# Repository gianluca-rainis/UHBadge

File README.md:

# UHBadge

Universal Hacker Badge - The ultimate badge for hackers.

## Author
The author of the whole project is: 
**Gianluca Rainis** - [gianluca-rainis](https://github.com/gianluca-rainis) on GitHub.

## License
### Hardware design files (schematics, PCB, BOM):
Licensed under [CERN-OHL-S v2.0](LICENSE-CERN-OHL-S.md)

### Software, firmware and documentation:
Licensed under the [MIT License](LICENSE-MIT.md)

## AI Disclaimer
**No AI was used in the conception, design, or engineering of the hardware.**
Every circuit and every design decision are the original work of the author.

*AI tools* were used as **writing assistants** for parts of the firmware, to help write technical drivers and low-level functions.
**All content has been reviewed, verified, and edited by the author.**

## Development Tools
- **PCB Design:** KiCad
- **Documentation and code:** Visual Studio Code

## PCB Manufacturing
The Gerber files for PCB manufacturing are available in the [`gerber/`](gerber/) directory.

## Project Structure
```
UHBadge/
├── CustomFootprints.pretty/  # Custom footprints
├── firmware/                 # The RP2350 firmware
├── gerber/                   # PCB manufacturing files (Gerber format)
├── images/                   # Documentation images
├── .gitattributes            # Gitattributes file
├── .gitignore                # Gitignore file
├── gerber.zip                # Zip folder with all the gerber files
├── UHBadge.kicad_pcb         # PCB layout file
├── UHBadge.kicad_pro         # KiCad project file
├── UHBadge.kicad_sch         # Schematic file
├── UHBadge.step              # 3D model
├── BOM.csv                   # Bill Of Materials
├── LICENSE-CERN-OHL-S.md     # CERN-OHL-S License
├── LICENSE-MIT.md            # MIT License
└── README.md                 # This file
```

## Technical Details
- **Size**: 70mm x 117.6mm
- **Layers**: 2
- **Supply Voltage**: 3v3

## Build the firmware
From the directory of the repo:
```bash
cd firmware/build

cmake ..
make -j$(sysctl -n hw.ncpu)
```

You'll find the `UHBadge.uf2` file in the `firmware/build` directory.

## Hardware
### Schematic

### PCB

### 3D Render

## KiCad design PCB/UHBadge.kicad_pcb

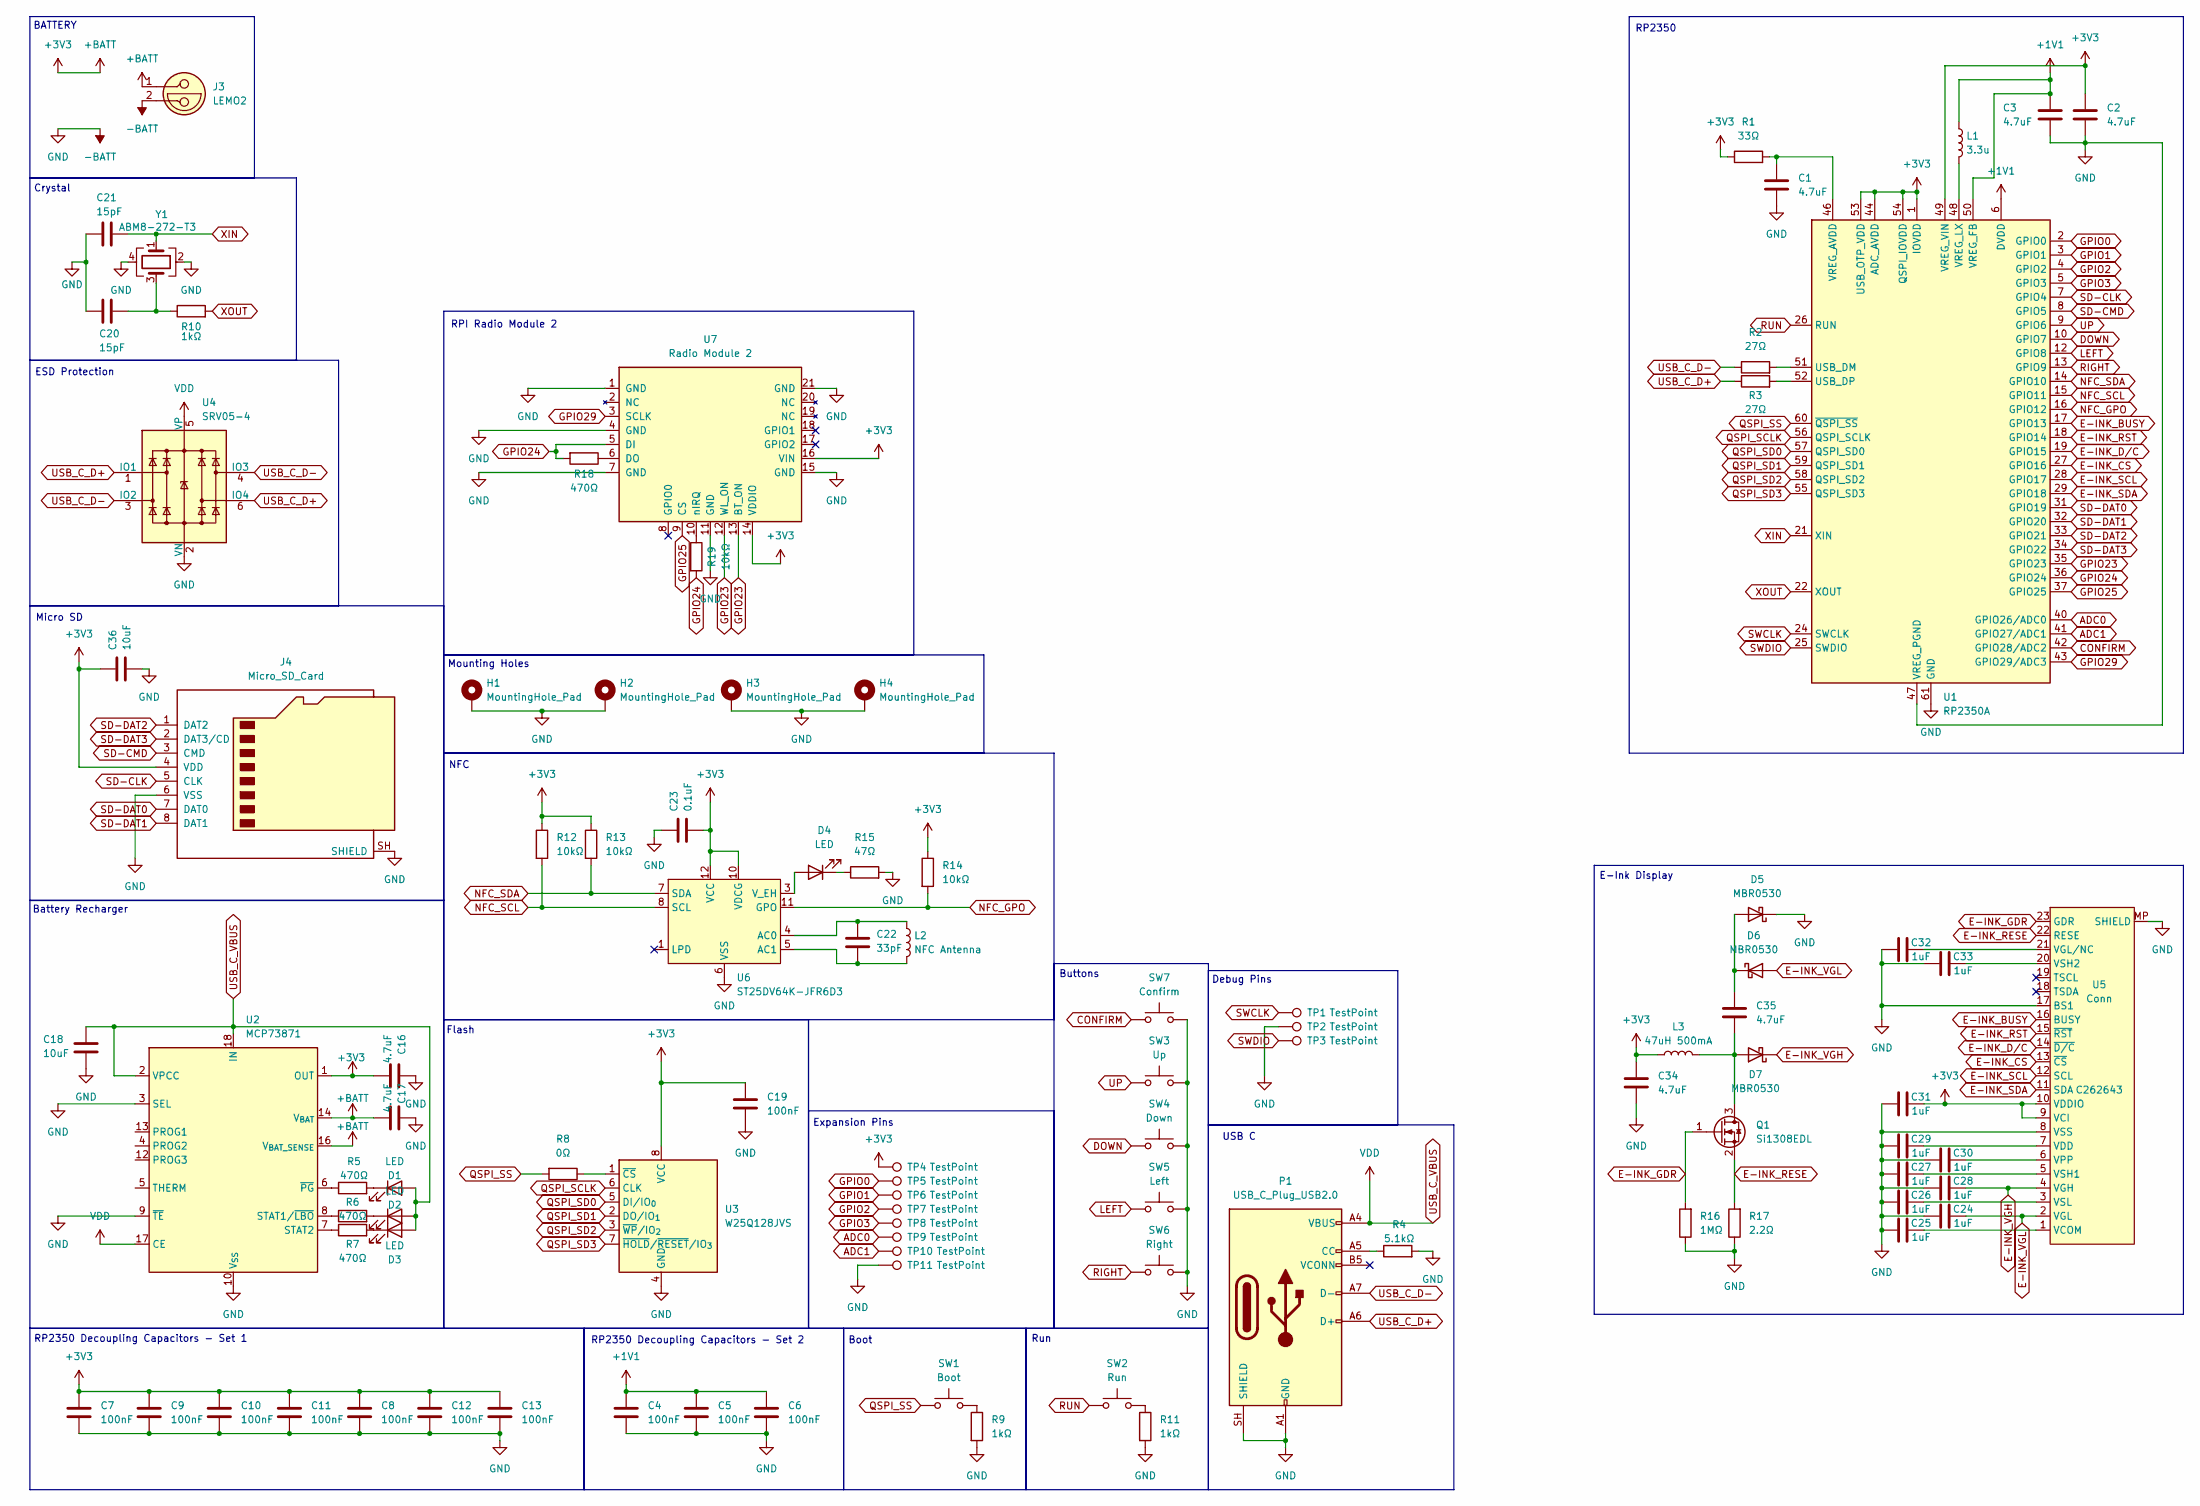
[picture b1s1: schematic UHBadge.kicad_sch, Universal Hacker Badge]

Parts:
C1, C2, C3, C16, C17, C34, C35: 4.7uF; C_0402_1005Metric
C4, C5, C6, C7, C8, C9, C10, C11, C12, C13, C19: 100nF; C_0402_1005Metric
C18, C36: 10uF; C_0402_1005Metric
C20, C21: 15pF; C_0402_1005Metric
C22: 33pF; C_0402_1005Metric
C23: 0.1uF; C_0402_1005Metric
C24, C25, C26, C27, C28, C29, C30, C31, C32, C33: 1uF; C_0402_1005Metric
D1, D2, D3, D4: LED; LED_0805_2012Metric
D5, D6, D7: MBR0530; D_SOD-123
H1, H2, H3, H4: MountingHole_Pad; MountingHole_2.2mm_M2_Pad_Via
J3: LEMO2; Molex_CLIK-Mate_502494-0270_1x02-1MP_P2.00mm_Horizontal
J4: Micro_SD_Card; microSD_HC_Hirose_DM3AT-SF-PEJM5
L1: 3.3u; Inductor
L2: NFC Antenna; NFC_Antenna
L3: 47uH 500mA; L_APV_ANR4018
P1: USB_C_Plug_USB2.0; USB_C_Receptacle_GCT_USB4105-xx-A_16P_TopMnt_Horizontal
Q1: Si1308EDL; SOT-323_SC-70
R1: 33Ω; R_0402_1005Metric
R2, R3: 27Ω; R_0402_1005Metric
R4: 5.1kΩ; R_0402_1005Metric
R5, R6, R7, R18: 470Ω; R_0402_1005Metric
R8: 0Ω; R_0402_1005Metric
R9, R10, R11: 1kΩ; R_0402_1005Metric
R12, R13, R14, R19: 10kΩ; R_0402_1005Metric
R15: 47Ω; R_0402_1005Metric
R16: 1MΩ; R_0402_1005Metric
R17: 2.2Ω; R_0402_1005Metric
SW1: Boot; SW_SPST_EVQP2_MiddlePushTravel_H2.5mm
SW2: Run; SW_SPST_EVQP2_MiddlePushTravel_H2.5mm
SW3: Up; SW_SPST_EVQP2_MiddlePushTravel_H2.5mm
SW4: Down; SW_SPST_EVQP2_MiddlePushTravel_H2.5mm
SW5: Left; SW_SPST_EVQP2_MiddlePushTravel_H2.5mm
SW6: Right; SW_SPST_EVQP2_MiddlePushTravel_H2.5mm
SW7: Confirm; SW_SPST_EVQP2_MiddlePushTravel_H2.5mm
TP1, TP2, TP3, TP4, TP5, TP6, TP7, TP8, TP9, TP10, TP11: TestPoint; TestPoint_Pad_D1.0mm
U1: RP2350A; QFN-60-1EP_7x7mm_P0.4mm_EP3.4x3.4mm
U2: MCP73871; QFN-20-1EP_4x4mm_P0.5mm_EP2.5x2.5mm
U3: W25Q128JVS; SOIC-8_5.3x5.3mm_P1.27mm
U4: SRV05-4; SOT-23-6
U5: Conn; Jushuo_AFC07-S24FCA-00_1x24-1MP_P0.50_Horizontal; LCSC Part # C262643
U6: ST25DV64K-JFR6D3; ST_UFDFPN-12-1EP_3x3mm_P0.5mm_EP1.4x2.55mm
U7: Radio Module 2; rpi_rmc20452t
Y1: ABM8-272-T3; Crystal_SMD_3225-4Pin_3.2x2.5mm; LCSC Part # C20625731

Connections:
+1V1: C3.1, C4.1, C5.1, C6.1, L1.1, U1.6 (DVDD), U1.23 (DVDD), U1.39 (DVDD), U1.50 (VREG_FB)
+3V3: C2.1, C7.1, C8.1, C9.1, C10.1, C11.1, C12.1, C13.1, C16.2, C17.2, C19.1, C23.2, C31.2, C34.1, C36.1, J3.1, J4.4 (VDD), L3.1, R1.1, R12.1, R13.1, R14.1, TP4.1 (1_1), U1.1 (IOVDD), U1.11 (IOVDD), U1.20 (IOVDD), U1.30 (IOVDD), U1.38 (IOVDD), U1.44 (ADC_AVDD), U1.45 (IOVDD), U1.49 (VREG_VIN), U1.53 (USB_OTP_VDD), U1.54 (QSPI_IOVDD), U2.1 (OUT), U2.14 (V_{BAT}), U2.15 (V_{BAT}), U2.16 (V_{BAT_SENSE}), U2.20 (OUT), U3.8 (VCC), U5.9 (VCI), U5.10 (VDDIO), U6.10 (VDCG), U6.12 (VCC), U7.14 (VDDIO), U7.16 (VIN)
-BATT: C1.2, C2.2, C3.2, C4.2, C5.2, C6.2, C7.2, C8.2, C9.2, C10.2, C11.2, C12.2, C13.2, C16.1, C17.1, C18.2, C19.2, C20.2, C21.1, C23.1, C24.1, C25.1, C26.1, C27.1, C28.1, C29.1, C30.1, C31.1, C32.1, C33.1, C34.2, C36.2, D5.1 (K), H1.1 (1_1), H2.1 (1_1), H3.1 (1_1), H4.1 (1_1), J3.2, J4.6 (VSS), J4.SH (SHIELD), P1.A1 (GND), P1.A12 (GND), P1.B1 (GND), P1.B12 (GND), P1.SH (SHIELD), R4.2, R9.2, R11.2, R15.2, R16.1, R17.1, SW3.2, SW4.2, SW5.2, SW6.2, SW7.2, TP2.1 (1_1), TP11.1 (1_1), U1.47 (VREG_PGND), U1.61 (GND), U2.3 (SEL), U2.9 (~TE), U2.10 (V_{SS}), U2.11 (V_{SS}), U2.21 (V_{SS}), U3.4 (GND), U4.2 (VN), U5.8 (VSS), U5.17 (BS1), U5.MP (SHIELD), U6.6 (VSS), U7.1 (GND), U7.4 (GND), U7.7 (GND), U7.11 (GND), U7.15 (GND), U7.21 (GND), Y1.2, Y1.4
ADC0: TP9.1 (1_1), U1.40 (GPIO26/ADC0)
ADC1: TP10.1 (1_1), U1.41 (GPIO27/ADC1)
CONFIRM: SW7.1, U1.42 (GPIO28/ADC2)
DOWN: SW4.1, U1.10 (GPIO7)
E-INK_BUSY: U1.17 (GPIO13), U5.16 (BUSY)
E-INK_CS: U1.27 (GPIO16), U5.13 (~CS)
E-INK_D/C: U1.19 (GPIO15), U5.14 (~D/C)
E-INK_GDR: Q1.1 (G), R16.2, U5.23 (GDR)
E-INK_RESE: Q1.2 (S), R17.2, U5.22 (RESE)
E-INK_RST: U1.18 (GPIO14), U5.15 (~RST)
E-INK_SCL: U1.28 (GPIO17), U5.12 (SCL)
E-INK_SDA: U1.29 (GPIO18), U5.11 (SDA)
E-INK_VGH: C28.2, D7.1 (K), U5.4 (VGH)
E-INK_VGL: C24.2, D6.2 (A), U5.2 (VGL)
GPIO0: TP5.1 (1_1), U1.2 (GPIO0)
GPIO1: TP6.1 (1_1), U1.3 (GPIO1)
GPIO2: TP7.1 (1_1), U1.4 (GPIO2)
GPIO3: TP8.1 (1_1), U1.5 (GPIO3)
GPIO23: U1.35 (GPIO23), U7.12 (WL_ON), U7.13 (BT_ON)
GPIO24: R18.2, R19.2, U1.36 (GPIO24), U7.5 (DI)
GPIO25: U1.37 (GPIO25), U7.9 (CS)
GPIO29: U1.43 (GPIO29/ADC3), U7.3 (SCLK)
LEFT: SW5.1, U1.12 (GPIO8)
NFC_GPO: R14.2, U1.16 (GPIO12), U6.11 (GPO)
NFC_SCL: R12.2, U1.15 (GPIO11), U6.8 (SCL)
NFC_SDA: R13.2, U1.14 (GPIO10), U6.7 (SDA)
unnamed: C20.1, R10.1, Y1.3
unnamed: D1.1 (K), R5.2
unnamed: D2.1 (K), R6.2
unnamed: D3.1 (K), R7.2
unnamed: D4.2 (A), U6.3 (V_EH)
unnamed: D4.1 (K), R15.1
unnamed: C35.1, D5.2 (A), D6.1 (K)
unnamed: C35.2, D7.2 (A), L3.2, Q1.3 (D)
unnamed: P1.A5 (CC), R4.1
unnamed: R9.1, SW1.2
unnamed: R11.1, SW2.2
unnamed: R2.2, U1.51 (USB_DM)
unnamed: R3.2, U1.52 (USB_DP)
unnamed: C1.1, R1.2, U1.46 (VREG_AVDD)
unnamed: L1.2, U1.48 (VREG_LX)
unnamed: R6.1, U2.8 (STAT1/~LBO)
unnamed: R7.1, U2.7 (STAT2)
unnamed: R5.1, U2.6 (~PG)
unnamed: R8.1, U3.1 (~CS)
unnamed: C25.2, U5.1 (VCOM)
unnamed: C29.2, U5.7 (VDD)
unnamed: C32.2, U5.21 (VGL/NC)
unnamed: C30.2, U5.6 (VPP)
unnamed: C27.2, U5.5 (VSH1)
unnamed: C33.2, U5.20 (VSH2)
unnamed: C26.2, U5.3 (VSL)
unnamed: C22.1, L2.1, U6.4 (AC0)
unnamed: C22.2, L2.2, U6.5 (AC1)
unnamed: R18.1, U7.6 (DO)
unnamed: R19.1, U7.10 (nIRQ)
QSPI_SCLK: U1.56 (QSPI_SCLK), U3.6 (CLK)
QSPI_SD0: U1.57 (QSPI_SD0), U3.5 (DI/IO_{0})
QSPI_SD1: U1.59 (QSPI_SD1), U3.2 (DO/IO_{1})
QSPI_SD2: U1.58 (QSPI_SD2), U3.3 (~WP/IO_{2})
QSPI_SD3: U1.55 (QSPI_SD3), U3.7 (~HOLD/~RESET/IO_{3})
QSPI_SS: R8.2, SW1.1, U1.60 (~QSPI_SS)
RIGHT: SW6.1, U1.13 (GPIO9)
RUN: SW2.1, U1.26 (RUN)
SD-CLK: J4.5 (CLK), U1.7 (GPIO4)
SD-CMD: J4.3 (CMD), U1.8 (GPIO5)
SD-DAT0: J4.7 (DAT0), U1.31 (GPIO19)
SD-DAT1: J4.8 (DAT1), U1.32 (GPIO20)
SD-DAT2: J4.1 (DAT2), U1.33 (GPIO21)
SD-DAT3: J4.2 (DAT3/CD), U1.34 (GPIO22)
SWCLK: TP1.1 (1_1), U1.24 (SWCLK)
SWDIO: TP3.1 (1_1), U1.25 (SWDIO)
UP: SW3.1, U1.9 (GPIO6)
USB_C_D+: P1.A6 (D+), R3.1, U4.1 (IO1), U4.6 (IO4)
USB_C_D-: P1.A7 (D-), R2.1, U4.3 (IO2), U4.4 (IO3)
USB_C_VBUS: C18.1, D1.2 (A), D2.2 (A), D3.2 (A), P1.A4 (VBUS), P1.A9 (VBUS), P1.B4 (VBUS), P1.B9 (VBUS), U2.2 (VPCC), U2.17 (CE), U2.18 (IN), U2.19 (IN), U4.5 (VP)
XIN: C21.2, U1.21 (XIN), Y1.1
XOUT: R10.2, U1.22 (XOUT)

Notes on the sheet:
USB C
NFC
Mounting Holes
Expansion Pins
Boot
Flash
Micro SD
RP2350 Decoupling Capacitors - Set 1
Debug Pins
RPI Radio Module 2
Battery Recharger
RP2350 Decoupling Capacitors - Set 2
BATTERY
Buttons
Crystal
ESD Protection
Run
E-Ink Display
RP2350

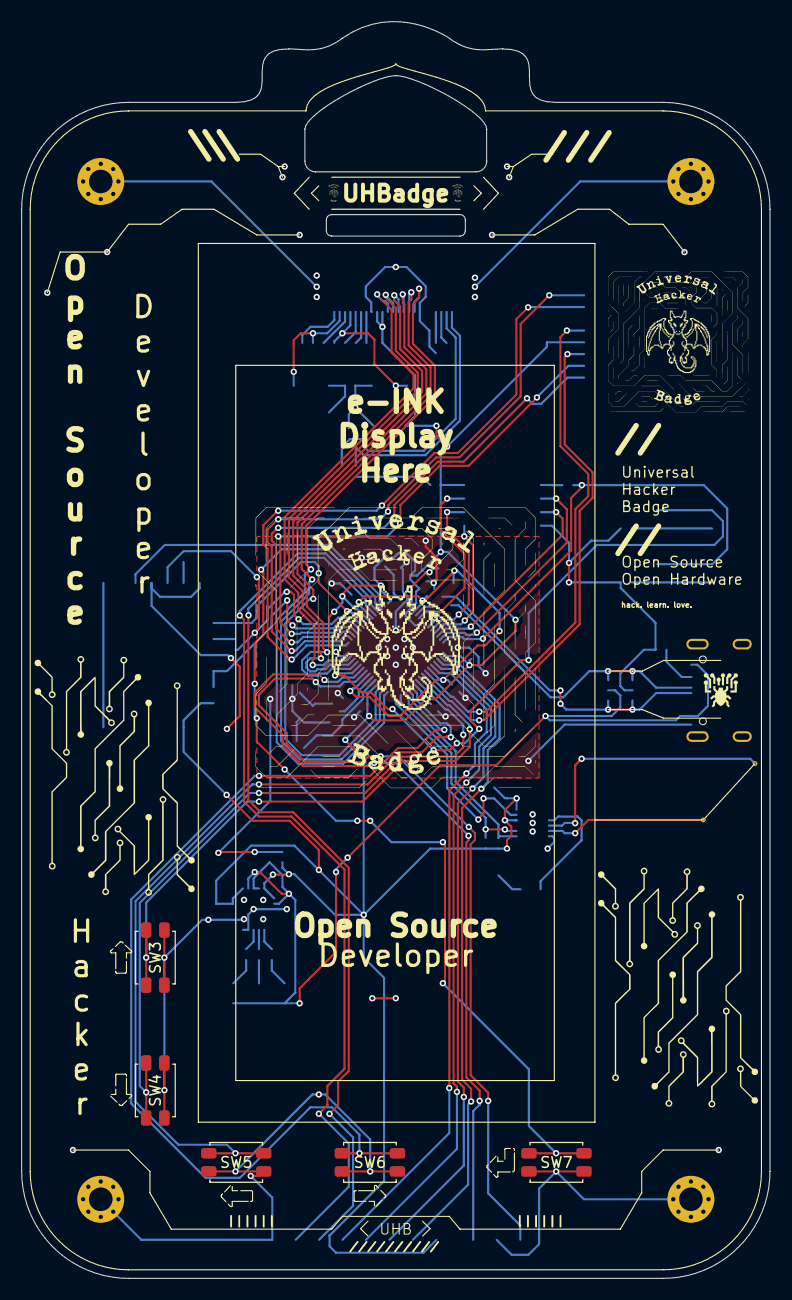
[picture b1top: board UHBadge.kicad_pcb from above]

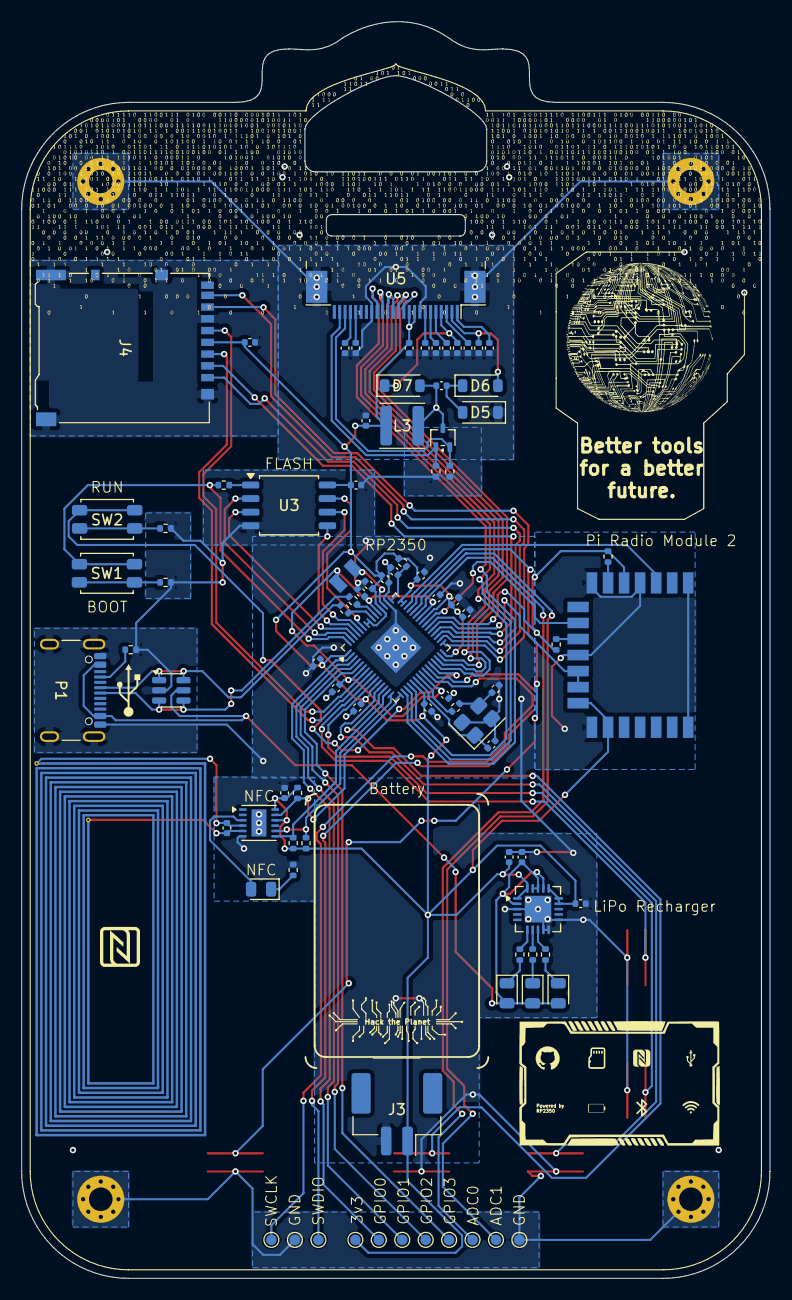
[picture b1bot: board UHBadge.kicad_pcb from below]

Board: 2 copper layers, 70.0 x 117.6 mm, 97 parts (88 on the bottom side), 81 nets.

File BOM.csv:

Reference,Quantity,Value,Footprint,Total Price,LCSC Part
"C1,C2,C3,C16,C17,C34,C35",7,4.7uF,Capacitor_SMD:C_0402_1005Metric,$0.85,C368809
"C4,C5,C6,C7,C8,C9,C10,C11,C12,C13,C19",11,100nF,Capacitor_SMD:C_0402_1005Metric,$0.46,C1525
"C18,C36",2,10uF,Capacitor_SMD:C_0402_1005Metric,$0.65,C315248
"C20,C21",2,15pF,Capacitor_SMD:C_0402_1005Metric,$0.36,C1548
C22,1,33pF,Capacitor_SMD:C_0402_1005Metric,$0.43,C70465
C23,1,0.1uF,Capacitor_SMD:C_0402_1005Metric,$0.46,C1525
"C24,C25,C26,C27,C28,C29,C30,C31,C32,C33",10,1uF,Capacitor_SMD:C_0402_1005Metric,$0.50,C52923
"D1,D2,D3,D4",4,LED,LED_SMD:LED_0805_2012Metric,$0.50,C25170728
"D5,D6,D7",3,MBR0530,Diode_SMD:D_SOD-123,$0.89,C725477
J3,1,LEMO2,Connector_Molex:Molex_CLIK-Mate_502494-0270_1x02-1MP_P2.00mm_Horizontal,$0.56,C587928
J4,1,Micro_SD_Card,Connector_Card:microSD_HC_Hirose_DM3AT-SF-PEJM5,$1.79,C114218
L1,1,3.3u,CustomFootprints:Inductor,$1.43,C42411119
L3,1,47uH 500mA,Inductor_SMD:L_APV_ANR4018,$0.79,C167808
P1,1,USB_C_Plug_USB2.0,Connector_USB:USB_C_Receptacle_GCT_USB4105-xx-A_16P_TopMnt_Horizontal,$1.31,C3020560
Q1,1,Si1308EDL,Package_TO_SOT_SMD:SOT-323_SC-70,$0.43,C7603347
R1,1,33Ω,Resistor_SMD:R_0402_1005Metric,$0.18,C453643
"R2,R3",2,27Ω,Resistor_SMD:R_0402_1005Metric,$0.20,C2909343
R4,1,5.1kΩ,Resistor_SMD:R_0402_1005Metric,$0.19,C2906874
"R5,R6,R7,R18",4,470Ω,Resistor_SMD:R_0402_1005Metric,$0.26,C25117
R8,1,0Ω,Resistor_SMD:R_0402_1005Metric,$0.36,C106231
"R9,R10,R11",3,1kΩ,Resistor_SMD:R_0402_1005Metric,$0.22,C11702
"R12,R13,R14,R19",4,10kΩ,Resistor_SMD:R_0402_1005Metric,$0.19,C71617
R15,1,47Ω,Resistor_SMD:R_0402_1005Metric,$0.18,C2909362
R16,1,1MΩ,Resistor_SMD:R_0402_1005Metric,$0.26,C93949
R17,1,2.2Ω,Resistor_SMD:R_0402_1005Metric,$0.20,C2906903
SW1,1,Boot,Button_Switch_SMD:SW_SPST_EVQP2_MiddlePushTravel_H2.5mm,$0.29,C2915174
SW2,1,Run,Button_Switch_SMD:SW_SPST_EVQP2_MiddlePushTravel_H2.5mm,$0.29,C2915174
SW3,1,Up,Button_Switch_SMD:SW_SPST_EVQP2_MiddlePushTravel_H2.5mm,$0.29,C2915174
SW4,1,Down,Button_Switch_SMD:SW_SPST_EVQP2_MiddlePushTravel_H2.5mm,$0.29,C2915174
SW5,1,Left,Button_Switch_SMD:SW_SPST_EVQP2_MiddlePushTravel_H2.5mm,$0.29,C2915174
SW6,1,Right,Button_Switch_SMD:SW_SPST_EVQP2_MiddlePushTravel_H2.5mm,$0.29,C2915174
SW7,1,Confirm,Button_Switch_SMD:SW_SPST_EVQP2_MiddlePushTravel_H2.5mm,$0.29,C2915174
U1,1,RP2350A,Package_DFN_QFN:QFN-60-1EP_7x7mm_P0.4mm_EP3.4x3.4mm,$1.30,C42411118
U2,1,MCP73871,Package_DFN_QFN:QFN-20-1EP_4x4mm_P0.5mm_EP2.5x2.5mm,$2.20,C511310
U3,1,W25Q128JVS,Package_SO:SOIC-8_5.3x5.3mm_P1.27mm,$2.53,C113767
U4,1,SRV05-4,Package_TO_SOT_SMD:SOT-23-6,$0.56,C2836319
U5,1,Conn,Connector_FFC-FPC:Jushuo_AFC07-S24FCA-00_1x24-1MP_P0.50_Horizontal,$0.66,C262567
U6,1,ST25DV64K-JFR6D3,Package_DFN_QFN:ST_UFDFPN-12-1EP_3x3mm_P0.5mm_EP1.4x2.55mm,$2.11,C2654868
U7,1,Radio Module 2,CustomFootprints:rpi_rmc20452t,"",""
Y1,1,ABM8-272-T3,Crystal:Crystal_SMD_3225-4Pin_3.2x2.5mm,$0.32,C19270184
"e-ink display",1,,,,""
"Li-Po battery",1,,,""

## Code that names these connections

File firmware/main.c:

/* 
    * Pinout:
    * 
    * GPIO0 - Expansion Pin
    * GPIO1 - Expansion Pin
    * GPIO2 - Expansion Pin
    * GPIO3 - Expansion Pin
    * GPIO4 - SD CLK
    * GPIO5 - SD CMD
    * GPIO6 - UP
    * GPIO7 - DOWN
    * GPIO8 - LEFT
    * GPIO9 - RIGHT
    * GPIO10 - NFC SDA
    * GPIO11 - NFC SCL
    * GPIO12 - NFC GPO
    * GPIO13 - E-INK BUSY
    * GPIO14 - E-INK RST
    * GPIO15 - E-INK D/C
    * GPIO16 - E-INK CS
    * GPIO17 - E-INK SCL
    * GPIO18 - E-INK SDA
    * GPIO19 - SD DAT0
    * GPIO20 - SD DAT1
    * GPIO21 - SD DAT2
    * GPIO22 - SD DAT3
    * GPIO23 - Pi Radio Module WL_ON + BT_ON
    * GPIO24 - Pi Radio Module DI + DO + nIRQ
    * GPIO25 - Pi Radio Module CS
    * GPIO26/ADC0 - Expansion Pin
    * GPIO27/ADC1 - Expansion Pin
    * GPIO28/ADC2 - UNCONNECTED
    * GPIO29/ADC3 - Pi Radio Module SCLK
*/

#include "firmware.h"
#include <stdbool.h>

int main() {
    setup();

    while (true)
    {
        loop();
    }

    return 0;
}

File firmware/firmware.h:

#include <stdio.h>
#include <stdbool.h>

#ifndef UHBADGE_FIRMWARE
    #define UHBADGE_FIRMWARE

    #define GPIO_EXPANSION_1 0
    #define GPIO_EXPANSION_2 1
    #define GPIO_EXPANSION_3 2
    #define GPIO_EXPANSION_4 3

    #define GPIO_SD_CLK 4
    #define GPIO_SD_CMD 5

    #define GPIO_UP 6
    #define GPIO_DOWN 7
    #define GPIO_LEFT 8
    #define GPIO_RIGHT 9

    #define GPIO_NFC_SDA 10
    #define GPIO_NFC_SCL 11
    #define GPIO_NFC_GPO 12

    #define GPIO_E_INK_BUSY 13
    #define GPIO_E_INK_RST 14
    #define GPIO_E_INK_DC 15
    #define GPIO_E_INK_CS 16
    #define GPIO_E_INK_SCL 17
    #define GPIO_E_INK_SDA 18

    #define GPIO_SD_DAT0 19
    #define GPIO_SD_DAT1 20
    #define GPIO_SD_DAT2 21
    #define GPIO_SD_DAT3 22

    #define GPIO_PI_RADIO_MODULE_WLON_BTON 23
    #define GPIO_PI_RADIO_MODULE_DI_DO_NIRQ 24
    #define GPIO_PI_RADIO_MODULE_CS 25

    #define GPIO_EXPANSION_ADC0 26
    #define GPIO_EXPANSION_ADC1 27
    
    #define GPIO_UNCONNECTED_ADC2 28

    #define GPIO_PI_RADIO_MODULE_SCLK 29

    // Main functions
    void setup();
    void loop();
#endif

#ifndef null
    #define null 0
#endif

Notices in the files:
README.md:
Hardware License
License: MIT License
